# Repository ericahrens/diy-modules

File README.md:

### DIY Eurorack Modules

This is repository containing my current Arduino/Teensy/Esp Projects aimed at DIY Eurorack projects. Currenty these are

* Magpie Modular Dodeca (Teensy) - MIDI -> CV
* Motivation Radio (ESP 32 Dev) - MIDI - CV
* Teensy 4.0 Oscilloscope Project (currently only on Breadboard)

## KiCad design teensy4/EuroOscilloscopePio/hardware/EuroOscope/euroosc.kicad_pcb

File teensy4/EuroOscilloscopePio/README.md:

### Experimental Eurorack Oscilloscope Teensy 4.0 Project

This is meant to be compiled and built with Platform IO and VS Code.
Please add the following libraries to the lib/ folder:

* [Adafruit_BusIO](https://github.com/adafruit/Adafruit_BusIO)
* [Adafruit-GFX](https://github.com/adafruit/Adafruit-GFX-Library)
* [Adafruit-ST7735](https://github.com/adafruit/Adafruit-ST7735-Library)
* [i2c_t3](https://github.com/nox771/i2c_t3)

A 2 channel Oscilloscope with Color OLED and very basic pitch detection.

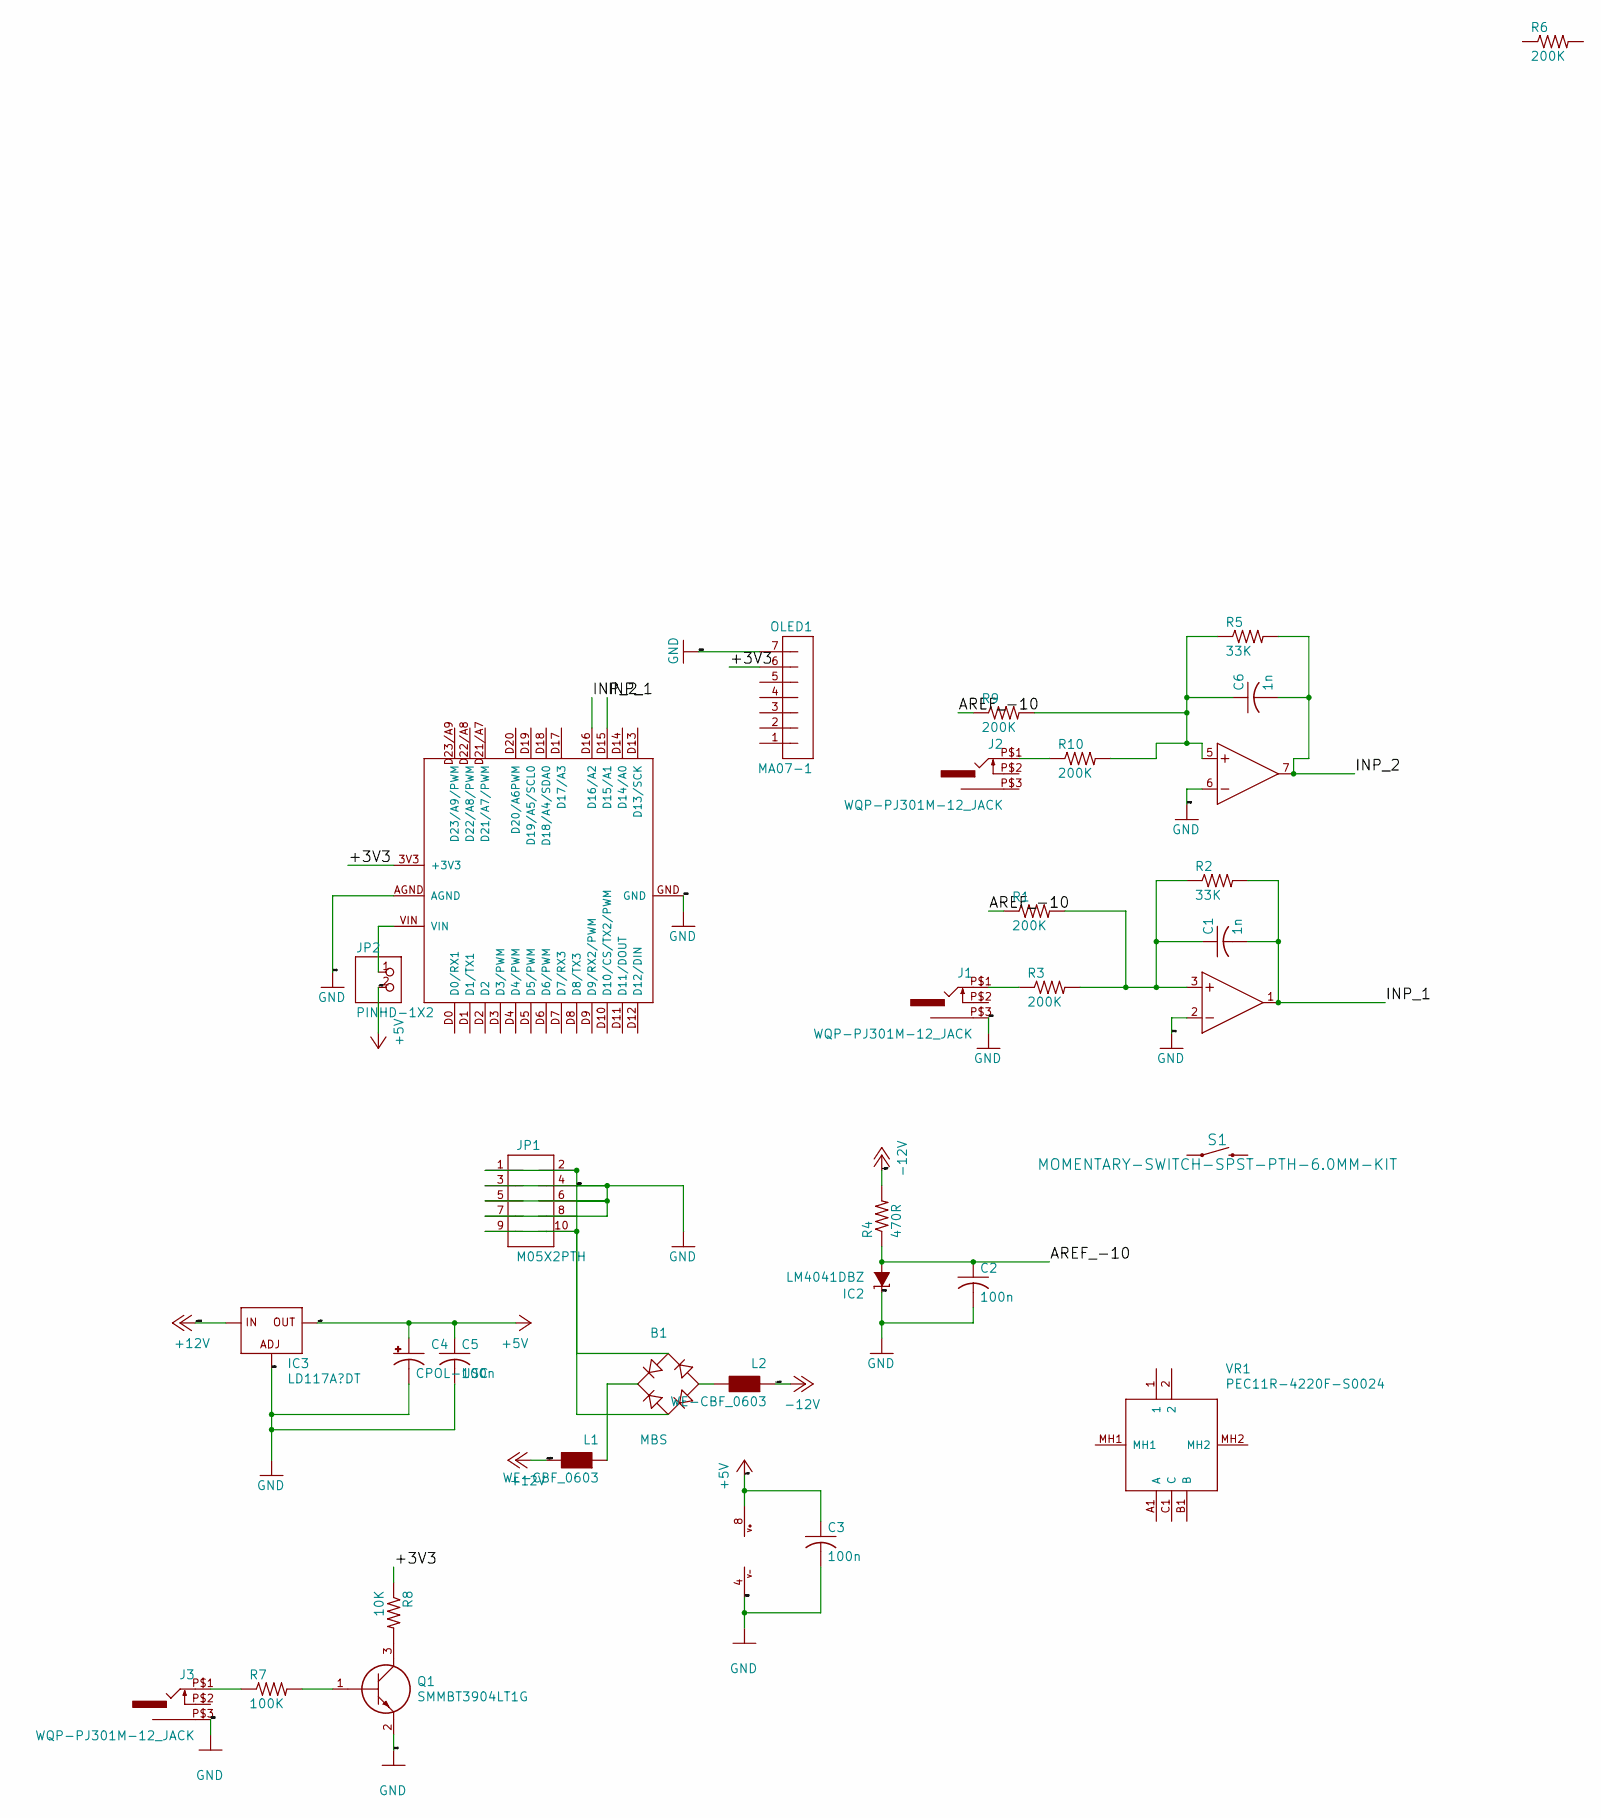
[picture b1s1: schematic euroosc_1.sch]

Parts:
B1: MBS; SOIC-4
C1, C6: 1n; C0603
C2, C3, C5: 100n; C0603
C4: CPOL-USC; PANASONIC_C
IC2: LM4041DBZ; DBZ_R-PDSO-G3
IC3: LD117A?DT; DPACK
IC4: MCP6002; SO08
J1, J2, J3: WQP-PJ301M-12_JACK
JP1: M05X2PTH; AVR_ICSP
JP2: PINHD-1X2; 1X02
L1, L2: WE-CBF_0603; 0603
OLED1: MA07-1
Q1: SMMBT3904LT1G; SOT96P237X111-3N
R1, R3, R6, R9, R10: 200K; R0603
R2, R5: 33K; R0603
R4: 470R; R0603
R7: 100K; R0603
R8: 10K; R0603
S1: MOMENTARY-SWITCH-SPST-PTH-6.0MM-KIT; TACTILE_SWITCH_PTH_6.0MM_KIT
U$1: TEENSY4.0RD; TEENSY-3.2RD
VR1: PEC11R-4220F-S0024; PEC11R4220FS0024

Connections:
+5V: C3.1, C4.+, C5.1, IC3.4 (OUT), IC4.8 (V+), JP2.2
+12V: IC3.3 (IN), L1.2
-12V: L2.1, R4.2
/euroosc_1/+3V3: OLED1.6, R8.1, U$1.3V3 (+3V3)
/euroosc_1/AREF_-10: C2.1, IC2.2 (A), R1.1, R4.1, R9.1
/euroosc_1/INP_1: C1.2, IC4.1 (OUT), R2.2, U$1.D15 (D15/A1)
/euroosc_1/INP_2: C6.2, IC4.7 (OUT), R5.2, U$1.D16 (D16/A2)
GND: B1.~1 (AC1), B1.~2 (AC2), C2.2, C3.2, C4.-, C5.2, IC2.1 (C), IC3.1 (ADJ), IC4.2 (-IN), IC4.4 (V-), IC4.6 (-IN), J1.P$3 (1), J3.P$3 (1), JP1.1, JP1.2, JP1.3, JP1.4, JP1.5, JP1.6, JP1.7, JP1.8, JP1.9, JP1.10, OLED1.7, Q1.2 (E), U$1.AGND, U$1.GND
unnamed: B1.+, L1.1
unnamed: B1.-, L2.2
unnamed: C1.1, IC4.3 (+IN), R1.2, R2.1, R3.2
unnamed: C6.1, IC4.5 (+IN), R5.1, R9.2, R10.2
unnamed: J1.P$1 (2), R3.1
unnamed: J2.P$1 (2), R10.1
unnamed: J3.P$1 (2), R7.1
unnamed: JP2.1, U$1.VIN
unnamed: Q1.1 (B), R7.2
unnamed: Q1.3 (C), R8.2

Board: 2 copper layers, 32 parts (0 on the bottom side), 18 nets, no tracks yet.

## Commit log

2021-03-01 more description
2021-03-01 Fixed to actual Version
2021-03-01 Added Experimental Eurorack Oscilloscope Project
2021-03-01 Fixed accidental delete
2021-03-01 Platform IO Variant Eurorscope added
2021-03-01 Fixed Links
2021-03-01 Platform IO for Dodeca
2021-03-01 Add first KiCad Designs
2021-05-21 some changes
2021-05-21 Fixed Display; added MIDI Thru
2021-05-21 Add Readme
2021-05-21 Fixed readme
2021-05-21 Minor Fix
